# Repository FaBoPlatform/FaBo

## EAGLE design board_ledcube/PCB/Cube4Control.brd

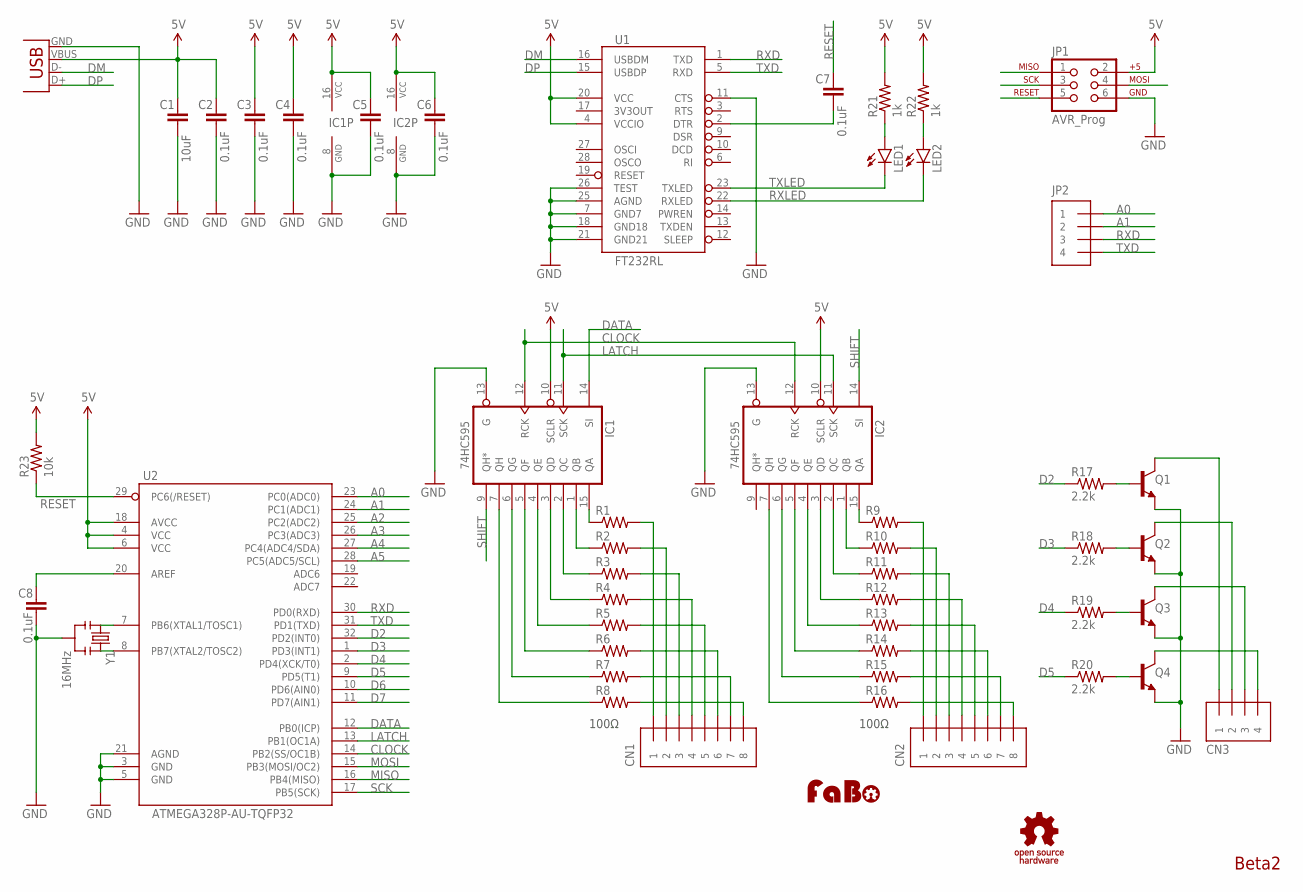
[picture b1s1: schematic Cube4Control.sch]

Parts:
C1: 10uF; EIA1206
C2, C3, C4, C5, C6, C7, C8: 0.1uF; EIA0603
CN1, CN2: PINHEAD-1X8; 1X8-SNEAKY
CN3: PINHEAD-1X4; 1X4-SNEAKY
IC1, IC2: 74HC595; SO16-3.9
JP1: AVR_Prog; TC2030-MCP
JP2: PINHEAD-1X4; 1X4-SNEAKY
LED1, LED2: LED-EIA0603; EIA0603-LED
Q1, Q2, Q3, Q4: NPN-2SC3325; SOT23-3
R1, R2, R3, R4, R5, R6, R7, R8, R9, R10, R11, R12, R13, R14, R15, R16: RES-EIA0603; EIA0603@1
R17, R18, R19, R20: 2.2k; EIA0603@1
R21, R22: 1k; EIA0603@1
R23: 10k; EIA0603@1
U1: FT232RL; SSOP28
U2: ATMEGA328P-AU-TQFP32; TQFP-32-08
U$2: LOGO_FABO-M; LOGO_FABO_M
U$4: LOGO_OSHW_T-M; LOGO_OSHW_T_M
USB1: USB-B-MICRO_SMD; USB_B_MICRO
Y1: 16MHz; RESONATOR_SMD

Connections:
5V: C1.1, C2.1, C3.1, C4.1, C5.1, C6.1, IC1.10 (SCLR), IC1.16 (VCC), IC2.10 (SCLR), IC2.16 (VCC), JP1.2, R21.2, R22.2, R23.2, U1.4 (VCCIO), U1.20 (VCC), U2.4 (VCC), U2.6 (VCC), U2.18 (AVCC), USB1.VBUS
A0: JP2.1, U2.23 (PC0(ADC0))
A1: JP2.2, U2.24 (PC1(ADC1))
A2: U2.25 (PC2(ADC2))
A3: U2.26 (PC3(ADC3))
A4: U2.27 (PC4(ADC4/SDA))
A5: U2.28 (PC5(ADC5/SCL))
AREF: C8.1, U2.20 (AREF)
CLOCK: IC1.12 (RCK), IC2.12 (RCK), U2.14 (PB2(SS/OC1B))
D2: R17.1, U2.32 (PD2(INT0))
D3: R18.1, U2.1 (PD3(INT1))
D4: R19.1, U2.2 (PD4(XCK/T0))
D5: R20.1, U2.9 (PD5(T1))
D6: U2.10 (PD6(AIN0))
D7: U2.11 (PD7(AIN1))
DATA: IC1.14 (SI), U2.12 (PB0(ICP))
DM: U1.16 (USBDM), USB1.D-
DP: U1.15 (USBDP), USB1.D+
DTR: C7.2, U1.2 (DTR)
GND: C1.2, C2.2, C3.2, C4.2, C5.2, C6.2, C8.2, IC1.8 (GND), IC1.13 (G), IC2.8 (GND), IC2.13 (G), JP1.6, Q1.2 (E), Q2.2 (E), Q3.2 (E), Q4.2 (E), U1.7 (GND7), U1.11 (CTS), U1.18 (GND18), U1.21 (GND21), U1.25 (AGND), U1.26 (TEST), U2.3 (GND), U2.5 (GND), U2.21 (AGND), USB1.GND, Y1.2
LATCH: IC1.11 (SCK), IC2.11 (SCK), U2.13 (PB1(OC1A))
MISO: JP1.1, U2.16 (PB4(MISO))
MOSI: JP1.4, U2.15 (PB3(MOSI/OC2))
unnamed: LED1.A, R21.1
unnamed: CN3.1, Q1.3 (C)
unnamed: CN3.2, Q2.3 (C)
unnamed: CN3.3, Q3.3 (C)
unnamed: U2.7 (PB6(XTAL1/TOSC1)), Y1.1
unnamed: U2.8 (PB7(XTAL2/TOSC2)), Y1.3
unnamed: CN3.4, Q4.3 (C)
unnamed: Q1.1 (B), R17.2
unnamed: Q2.1 (B), R18.2
unnamed: Q3.1 (B), R19.2
unnamed: Q4.1 (B), R20.2
unnamed: CN2.1, R9.2
unnamed: CN2.2, R10.2
unnamed: CN2.3, R11.2
unnamed: CN2.4, R12.2
unnamed: CN2.5, R13.2
unnamed: CN2.6, R14.2
unnamed: CN2.7, R15.2
unnamed: CN2.8, R16.2
unnamed: IC2.15 (QA), R9.1
unnamed: IC2.1 (QB), R10.1
unnamed: IC2.2 (QC), R11.1
unnamed: IC2.3 (QD), R12.1
unnamed: IC2.4 (QE), R13.1
unnamed: IC2.5 (QF), R14.1
unnamed: IC2.6 (QG), R15.1
unnamed: IC1.15 (QA), R1.1
unnamed: IC1.1 (QB), R2.1
unnamed: LED2.A, R22.1
unnamed: IC1.2 (QC), R3.1
unnamed: IC1.3 (QD), R4.1
unnamed: IC2.7 (QH), R16.1
unnamed: IC1.4 (QE), R5.1
unnamed: IC1.5 (QF), R6.1
unnamed: IC1.6 (QG), R7.1
unnamed: IC1.7 (QH), R8.1
unnamed: CN1.1, R1.2
unnamed: CN1.2, R2.2
unnamed: CN1.3, R3.2
unnamed: CN1.4, R4.2
unnamed: CN1.5, R5.2
unnamed: CN1.6, R6.2
unnamed: CN1.7, R7.2
unnamed: CN1.8, R8.2
RESET: C7.1, JP1.5, R23.1, U2.29 (PC6(/RESET))
RXD: JP2.3, U1.1 (TXD), U2.30 (PD0(RXD))
RXLED: LED2.C, U1.22 (RXLED)
SCK: JP1.3, U2.17 (PB5(SCK))
SHIFT: IC1.9 (QH*), IC2.14 (SI)
TXD: JP2.4, U1.5 (RXD), U2.31 (PD1(TXD))
TXLED: LED1.C, U1.23 (TXLED)

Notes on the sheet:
Beta2
100Ω

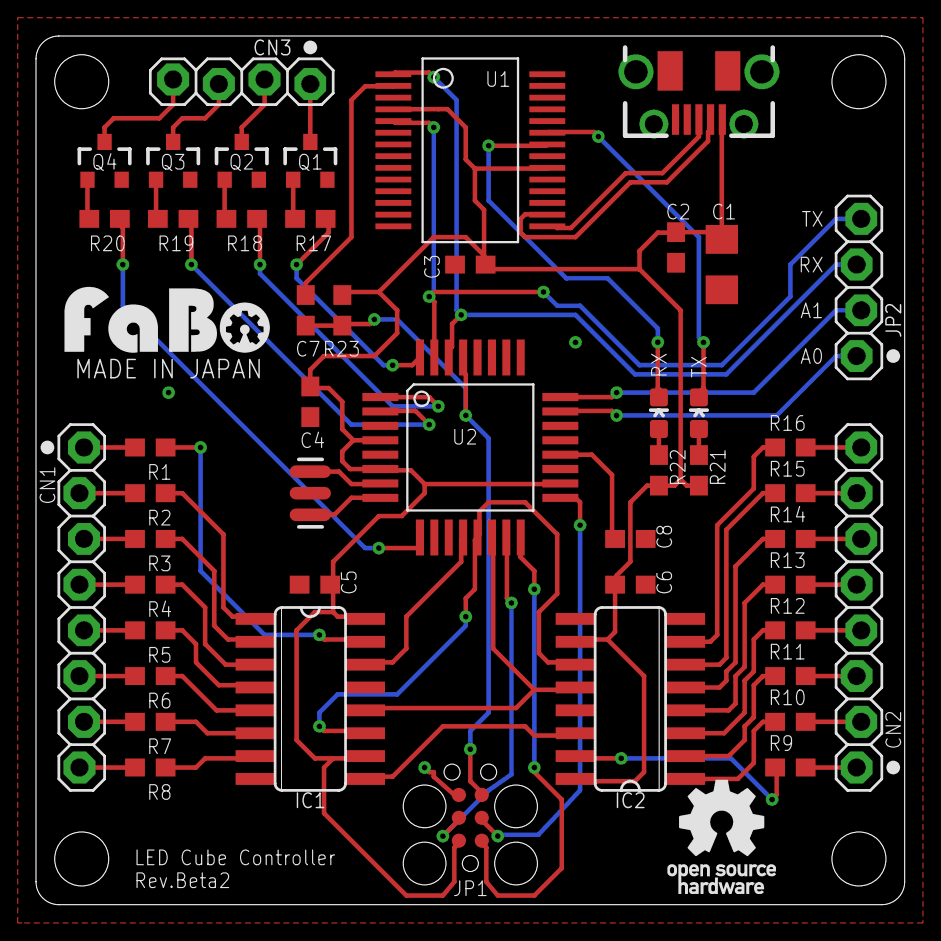
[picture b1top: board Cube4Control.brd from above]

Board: 2 copper layers, 48.3 x 48.3 mm, 50 parts (0 on the bottom side), 68 nets.

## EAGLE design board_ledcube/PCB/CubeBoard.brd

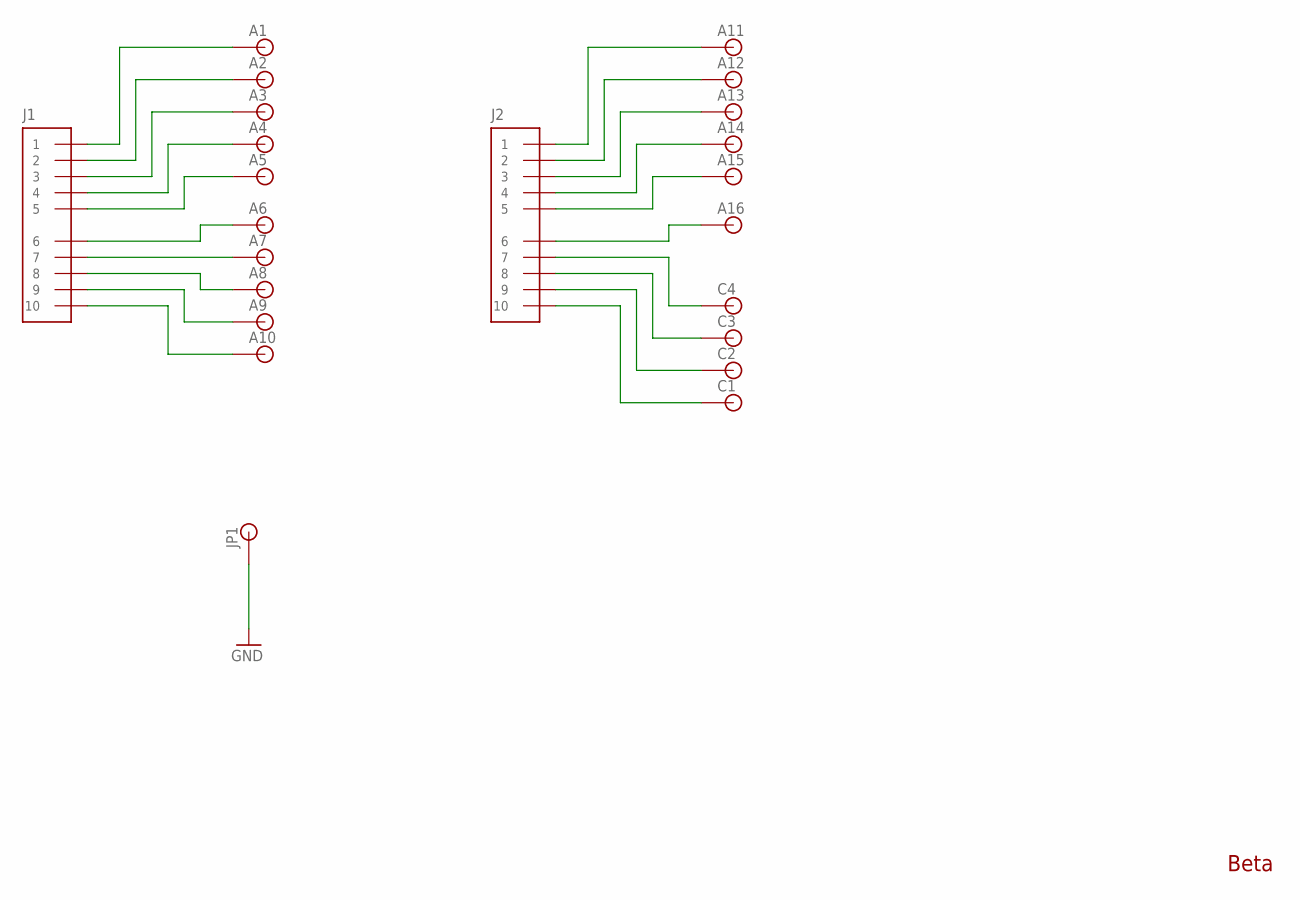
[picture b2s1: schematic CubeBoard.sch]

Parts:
A1: anode1; PIN-1X1
A2: anode2; PIN-1X1
A3: anode3; PIN-1X1
A4: anode4; PIN-1X1
A5: anode5; PIN-1X1
A6: anode6; PIN-1X1
A7: anode7; PIN-1X1
A8: anode8; PIN-1X1
A9: anode9; PIN-1X1
A10: anode10; PIN-1X1
A11: anode11; PIN-1X1
A12: anode12; PIN-1X1
A13: anode13; PIN-1X1
A14: anode14; PIN-1X1
A15: anode15; PIN-1X1
A16: anode16; PIN-1X1
C1: cathode1; PIN-1X1
C2: cathode2; PIN-1X1
C3: cathode3; PIN-1X1
C4: cathode4; PIN-1X1
J1, J2: PINHEAD-1X10; 1X10-SNEAKY
JP1: PIN-1X1

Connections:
GND: JP1.1
unnamed: A1.1, J1.1
unnamed: A2.1, J1.2
unnamed: A3.1, J1.3
unnamed: A4.1, J1.4
unnamed: A5.1, J1.5
unnamed: A6.1, J1.6
unnamed: A7.1, J1.7
unnamed: A8.1, J1.8
unnamed: A9.1, J1.9
unnamed: A10.1, J1.10
unnamed: A11.1, J2.1
unnamed: A12.1, J2.2
unnamed: A13.1, J2.3
unnamed: A14.1, J2.4
unnamed: A15.1, J2.5
unnamed: A16.1, J2.6
unnamed: C4.1, J2.7
unnamed: C3.1, J2.8
unnamed: C2.1, J2.9
unnamed: C1.1, J2.10

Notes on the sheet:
Beta

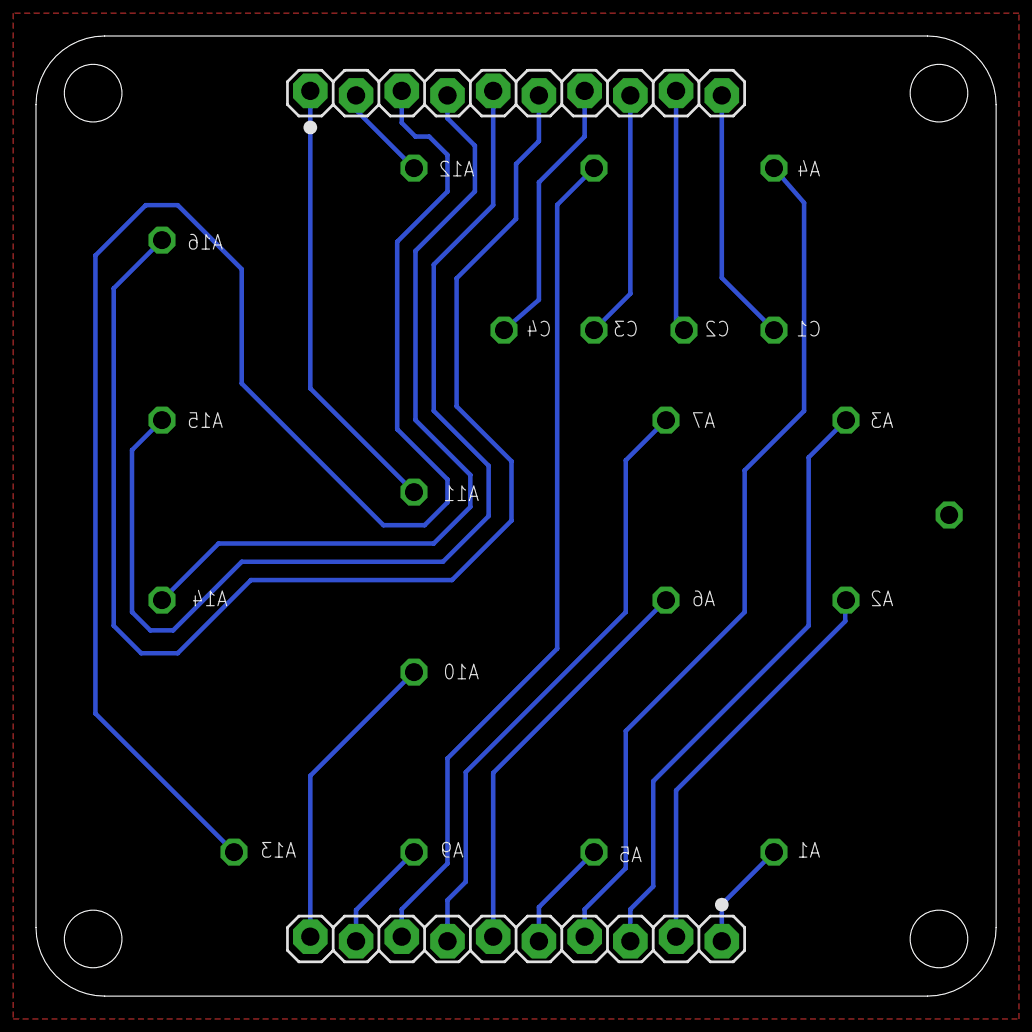
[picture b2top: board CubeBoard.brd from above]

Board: 2 copper layers, 53.3 x 53.3 mm, 23 parts (0 on the bottom side), 20 nets.

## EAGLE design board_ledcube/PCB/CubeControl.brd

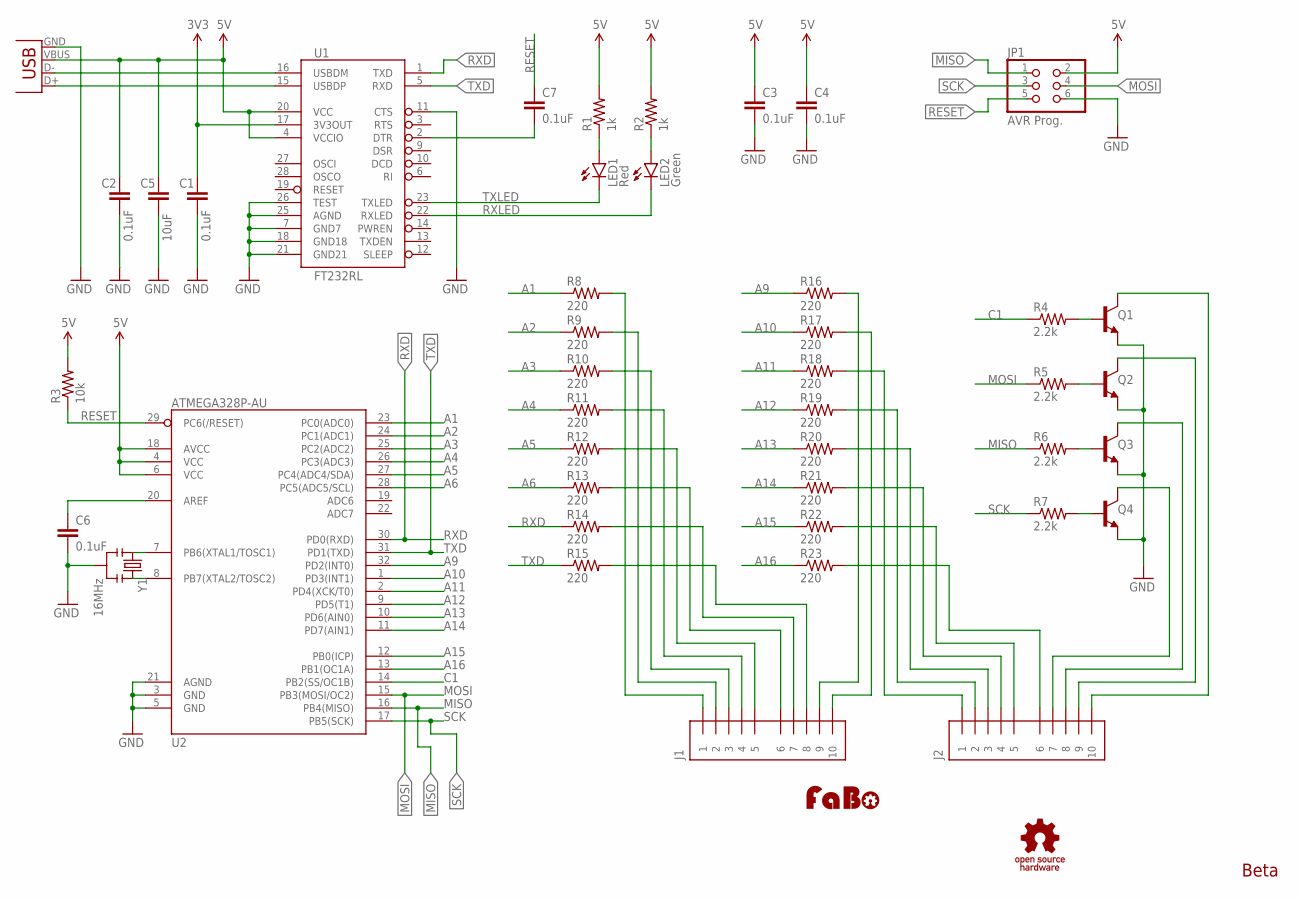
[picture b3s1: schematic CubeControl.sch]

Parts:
C1, C2, C3, C4, C6, C7: 0.1uF; EIA0603-CAP
C5: 10uF; EIA1206@1
J1, J2: PINHEAD-1X10; 1X10-SNEAKY
JP1: AVR Prog.; 2X03
LED1: Red; EIA0603-LED
LED2: Green; EIA0603-LED
Q1, Q2, Q3, Q4: NPN-2SC3325; SOT23-3
R1, R2: 1k; EIA0603-RES
R3: 10k; EIA0603-RES
R4, R5, R6, R7: 2.2k; EIA0603
R8, R9, R10, R11, R12, R13, R14, R15, R16, R17, R18, R19, R20, R21, R22, R23: 220; EIA0603
U1: FT232RL; SSOP28
U2: ATMEGA328P-AU; TQFP-32-08
U$2: LOGO_OSHW_T-S; LOGO_OSHW_T_S
U$3: LOGO_FABO-M; LOGO_FABO_M
USB1: USB-B-MICRO_SMD; USB_B_MICRO
Y1: 16MHz; RESONATOR_SMD

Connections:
3V3: C1.1, U1.17 (3V3OUT)
5V: C2.1, C3.1, C4.1, C5.1, JP1.2, R1.2, R2.2, R3.2, U1.4 (VCCIO), U1.20 (VCC), U2.4 (VCC), U2.6 (VCC), U2.18 (AVCC), USB1.VBUS
A1: R8.1, U2.23 (PC0(ADC0))
A2: R9.1, U2.24 (PC1(ADC1))
A3: R10.1, U2.25 (PC2(ADC2))
A4: R11.1, U2.26 (PC3(ADC3))
A5: R12.1, U2.27 (PC4(ADC4/SDA))
A6: R13.1, U2.28 (PC5(ADC5/SCL))
A9: R16.1, U2.32 (PD2(INT0))
A10: R17.1, U2.1 (PD3(INT1))
A11: R18.1, U2.2 (PD4(XCK/T0))
A12: R19.1, U2.9 (PD5(T1))
A13: R20.1, U2.10 (PD6(AIN0))
A14: R21.1, U2.11 (PD7(AIN1))
A15: R22.1, U2.12 (PB0(ICP))
A16: R23.1, U2.13 (PB1(OC1A))
C1: R4.1, U2.14 (PB2(SS/OC1B))
GND: C1.2, C2.2, C3.2, C4.2, C5.2, C6.2, JP1.6, Q1.2 (E), Q2.2 (E), Q3.2 (E), Q4.2 (E), U1.7 (GND7), U1.11 (CTS), U1.18 (GND18), U1.21 (GND21), U1.25 (AGND), U1.26 (TEST), U2.3 (GND), U2.5 (GND), U2.21 (AGND), USB1.GND, Y1.2
MISO: JP1.1, R6.1, U2.16 (PB4(MISO))
MOSI: JP1.4, R5.1, U2.15 (PB3(MOSI/OC2))
unnamed: LED1.A, R1.1
unnamed: LED2.A, R2.1
unnamed: J1.1, R8.2
unnamed: J1.2, R9.2
unnamed: U2.7 (PB6(XTAL1/TOSC1)), Y1.1
unnamed: U2.8 (PB7(XTAL2/TOSC2)), Y1.3
unnamed: C6.1, U2.20 (AREF)
unnamed: J1.3, R10.2
unnamed: J1.4, R11.2
unnamed: J1.5, R12.2
unnamed: J1.6, R13.2
unnamed: J1.7, R14.2
unnamed: J1.8, R15.2
unnamed: J1.9, R16.2
unnamed: J1.10, R17.2
unnamed: J2.1, R18.2
unnamed: J2.2, R19.2
unnamed: J2.3, R20.2
unnamed: J2.4, R21.2
unnamed: J2.5, R22.2
unnamed: J2.6, R23.2
unnamed: C7.2, U1.2 (DTR)
unnamed: J2.10, Q1.3 (C)
unnamed: J2.9, Q2.3 (C)
unnamed: J2.8, Q3.3 (C)
unnamed: J2.7, Q4.3 (C)
unnamed: Q4.1 (B), R7.2
unnamed: Q3.1 (B), R6.2
unnamed: Q2.1 (B), R5.2
unnamed: Q1.1 (B), R4.2
RESET: C7.1, JP1.5, R3.1, U2.29 (PC6(/RESET))
RXD: R14.1, U1.1 (TXD), U2.30 (PD0(RXD))
RXLED: LED2.C, U1.22 (RXLED)
SCK: JP1.3, R7.1, U2.17 (PB5(SCK))
TXD: R15.1, U1.5 (RXD), U2.31 (PD1(TXD))
TXLED: LED1.C, U1.23 (TXLED)
USB_D+: U1.15 (USBDP), USB1.D+
USB_D-: U1.16 (USBDM), USB1.D-

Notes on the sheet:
Beta

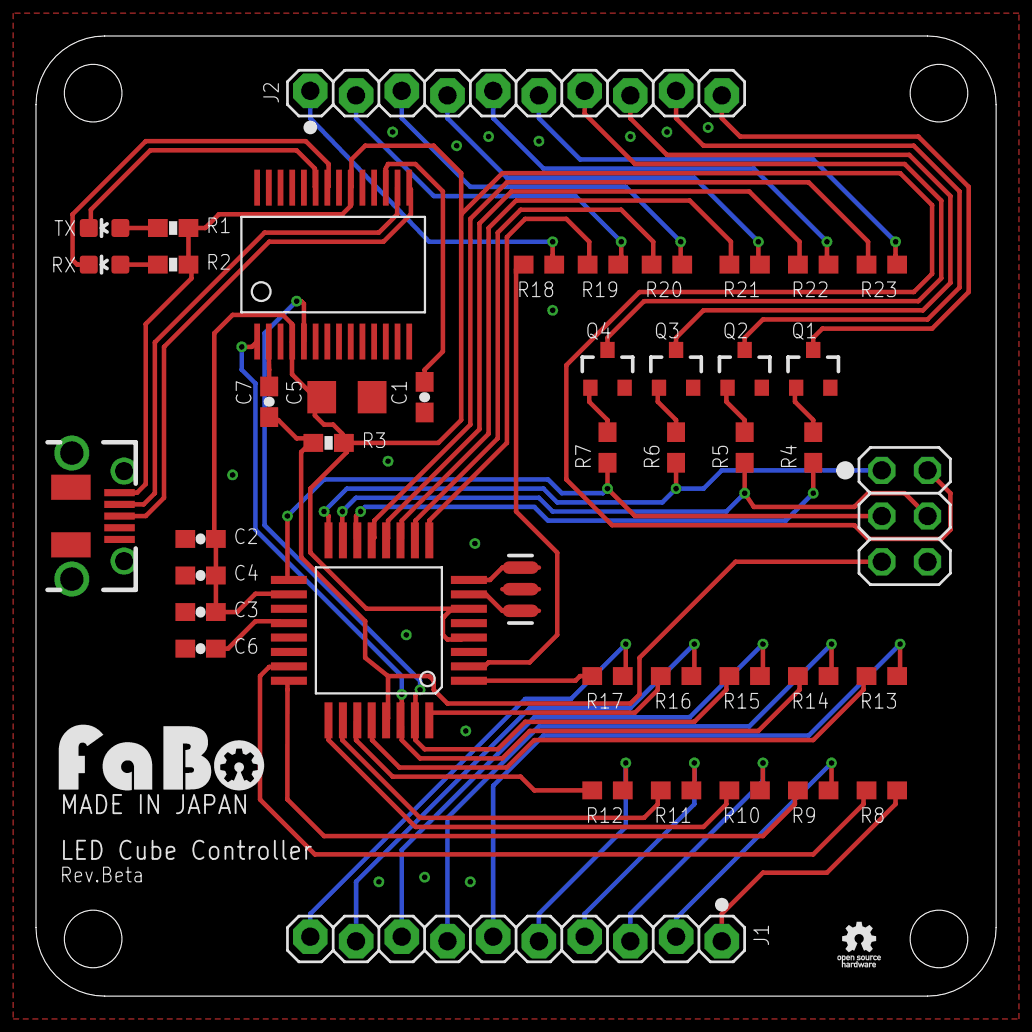
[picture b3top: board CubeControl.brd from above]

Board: 2 copper layers, 53.3 x 53.3 mm, 45 parts (0 on the bottom side), 58 nets.

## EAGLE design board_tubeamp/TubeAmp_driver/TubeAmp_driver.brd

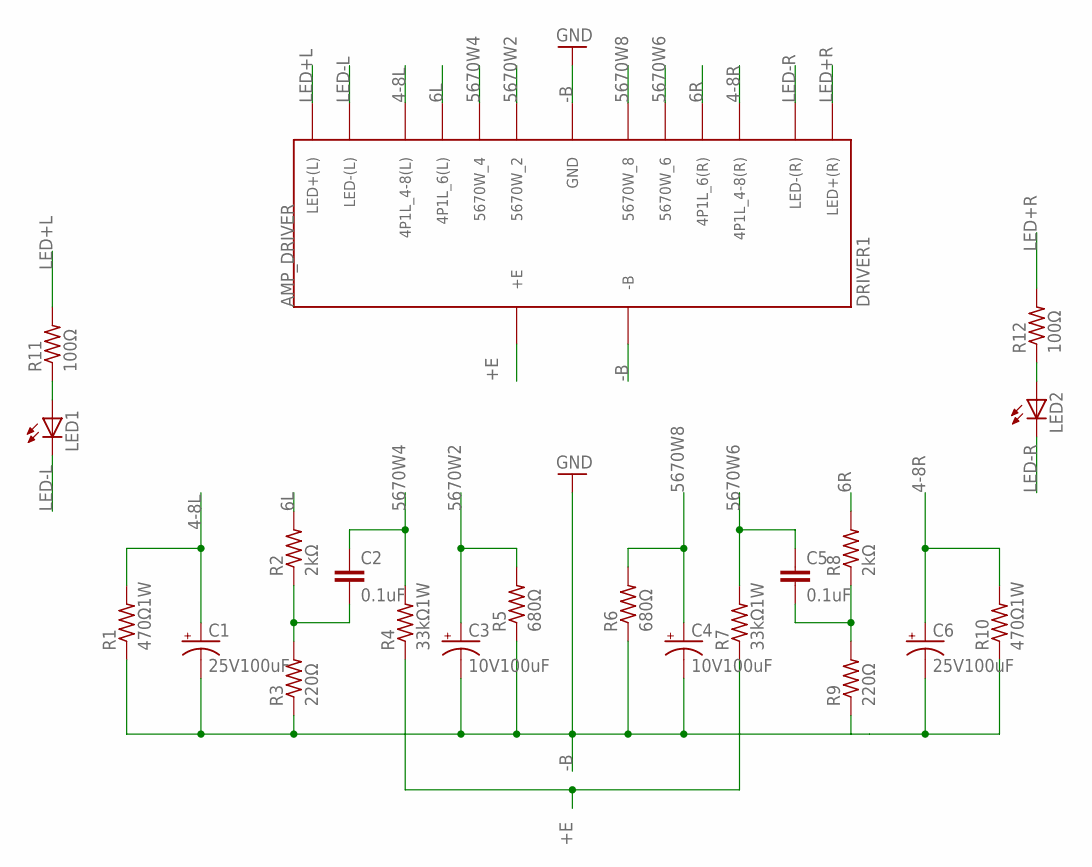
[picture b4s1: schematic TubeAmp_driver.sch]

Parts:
C1, C6: 25V100uF; 100UF25V_S3_NO_VALUE
C2, C5: 0.1uF; C12.5B6_NO_VALUE
C3, C4: 10V100uF; 100UF25V_S3_NO_VALUE
DRIVER1: AMP_DRIVER
LED1, LED2: LED; LED3MM
R1, R10: 470Ω1W; RESISTOR_1W
R2, R8: 2kΩ; RESISTOR_1/4W
R3, R9: 220Ω; RESISTOR_1/4W
R4, R7: 33kΩ1W; RESISTOR_1W
R5, R6: 680Ω; RESISTOR_1/4W
R11, R12: 100Ω; RESISTOR_1/4W

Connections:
4-8L: C1.1 (+), DRIVER1.4P1L_4-8L (4P1L_4-8(L)), R1.2
4-8R: C6.1 (+), DRIVER1.4P1L_4-8R (4P1L_4-8(R)), R10.2
6L: DRIVER1.4P1L_6L (4P1L_6(L)), R2.2
6R: DRIVER1.4P1L_6R (4P1L_6(R)), R8.2
5670W2: C3.1 (+), DRIVER1.5670W_2, R5.2
5670W4: C2.1, DRIVER1.5670W_4, R4.2
5670W6: C5.1, DRIVER1.5670W_6, R7.2
5670W8: C4.1 (+), DRIVER1.5670W_8, R6.2
+E: DRIVER1.+E, R4.1, R7.1
-B: C1.2 (-), C3.2 (-), C4.2 (-), C6.2 (-), DRIVER1.-B, DRIVER1.GND, R1.1, R3.1, R5.1, R6.1, R9.1, R10.1
LED+L: DRIVER1.LED+_L (LED+(L)), R11.2
LED+R: DRIVER1.LED+_R (LED+(R)), R12.2
LED-L: DRIVER1.LED-_L (LED-(L)), LED1.K (C)
LED-R: DRIVER1.LED-_R (LED-(R)), LED2.K (C)
unnamed: C2.2, R2.1, R3.2
unnamed: LED1.A, R11.1
unnamed: LED2.A, R12.1
unnamed: C5.2, R8.1, R9.2

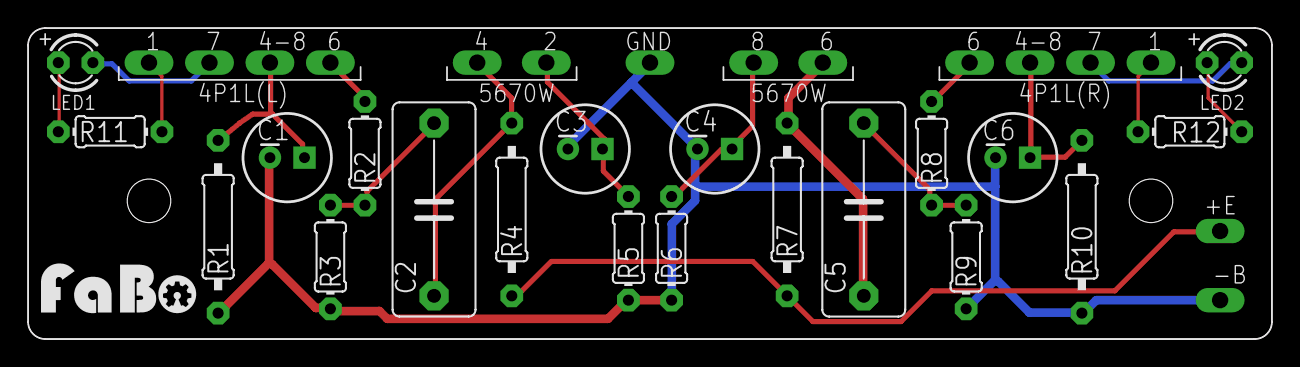
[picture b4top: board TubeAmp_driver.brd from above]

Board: 2 copper layers, 91.4 x 22.9 mm, 22 parts (0 on the bottom side), 18 nets.

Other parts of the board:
U$1: LOGO_FABO_M

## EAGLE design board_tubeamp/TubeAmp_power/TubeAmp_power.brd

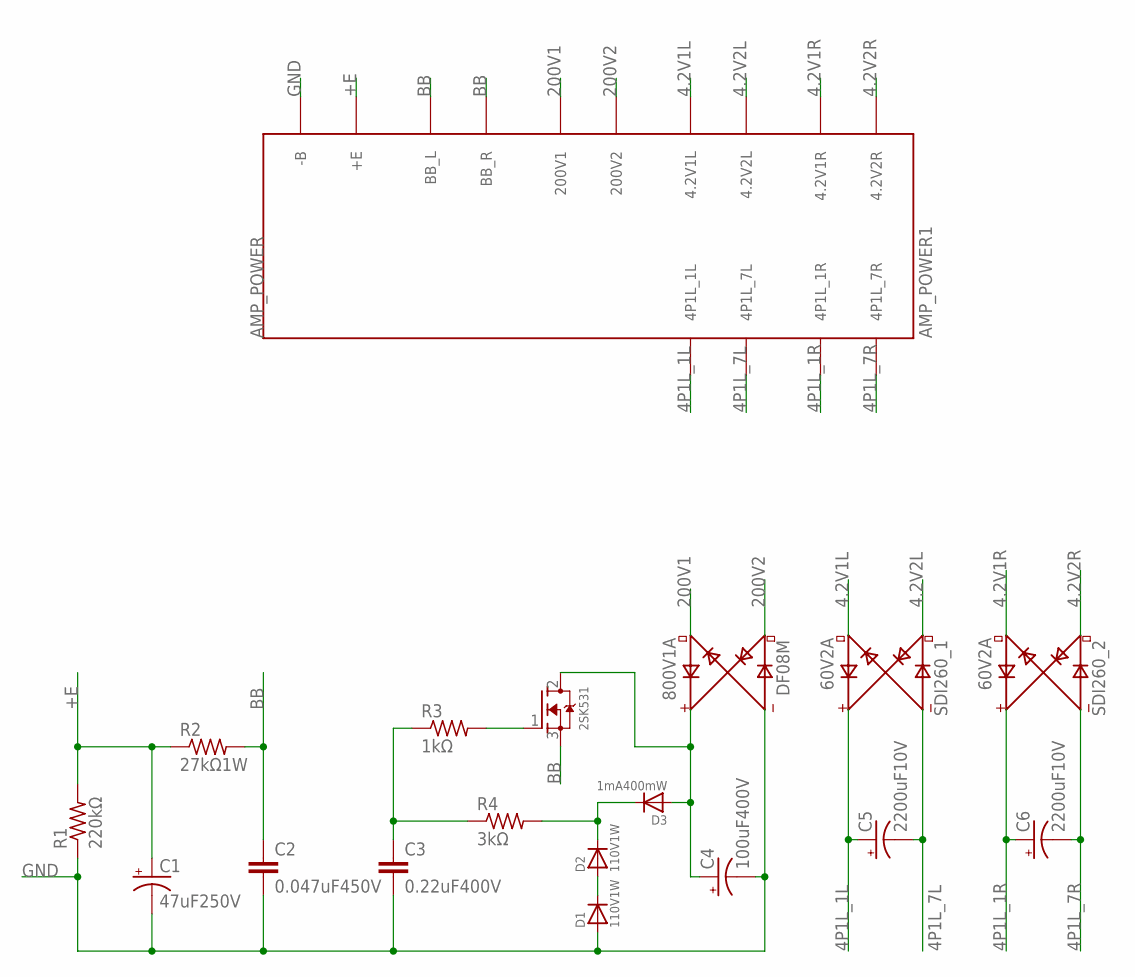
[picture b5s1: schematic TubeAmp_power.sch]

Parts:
2SK531: MOSFET_NN-CHANNEL; MOSFET-N
AMP_POWER1: AMP_POWER
C1: 47uF250V; 47UF250V_S5_NO_VALUE
C2: 0.047uF450V; C15B6_NO_VALUE
C3: 0.22uF400V; C10B6_NO_VALUE
C4: 100uF400V; 100UF400V_S6_NO_VALUE
C5, C6: 2200uF10V; 47UF250V_S5_NO_VALUE
D1, D2: 110V1W; DIODE_NO_VALUE
D3: 1mA400mW; DIODE_NO_VALUE
DF08M: 800V1A; RECTIFER
R1: 220kΩ; RESISTOR_1/2W
R2: 27kΩ1W; RESISTOR_1W
R3: 1kΩ; RESISTOR_1/4W
R4: 3kΩ; RESISTOR_1/4W
SDI260_1, SDI260_2: 60V2A; RECTIFER

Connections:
4.2V1L: AMP_POWER1.4.2V1(L) (4.2V1L), SDI260_1.AC2
4.2V1R: AMP_POWER1.4.2V1(R) (4.2V1R), SDI260_2.AC2
4.2V2L: AMP_POWER1.4.2V2(L) (4.2V2L), SDI260_1.AC1
4.2V2R: AMP_POWER1.4.2V2(R) (4.2V2R), SDI260_2.AC1
4P1L_1L: AMP_POWER1.4P1L_1(L) (4P1L_1L), C5.1 (+), SDI260_1.+
4P1L_1R: AMP_POWER1.4P1L_1(R) (4P1L_1R), C6.1 (+), SDI260_2.+
4P1L_7L: AMP_POWER1.4P1L_7(L) (4P1L_7L), C5.2 (-), SDI260_1.-
4P1L_7R: AMP_POWER1.4P1L_7(R) (4P1L_7R), C6.2 (-), SDI260_2.-
200V1: AMP_POWER1.200V1, DF08M.AC2
200V2: AMP_POWER1.200V2, DF08M.AC1
+E: AMP_POWER1.+E, C1.1 (+), R1.2, R2.1
BB: 2SK531.3 (S), AMP_POWER1.BB(L) (BB_L), AMP_POWER1.BB(R) (BB_R), C2.1, R2.2
GND: AMP_POWER1.-B, C1.2 (-), C2.2, C3.2, C4.2 (-), D1.A, DF08M.-, R1.1
unnamed: 2SK531.1 (G), R3.2
unnamed: 2SK531.2 (D), C4.1 (+), D3.A, DF08M.+
unnamed: C3.1, R3.1, R4.1
unnamed: D2.K, D3.K, R4.2
unnamed: D1.K, D2.A

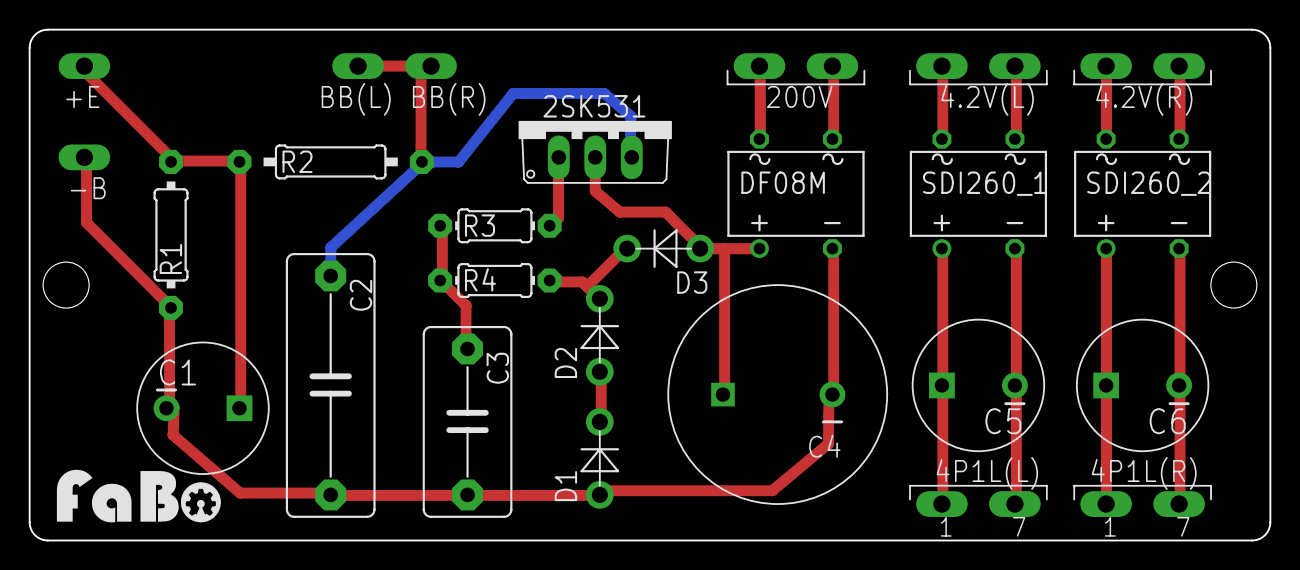
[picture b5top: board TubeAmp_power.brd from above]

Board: 2 copper layers, 86.4 x 35.6 mm, 19 parts (0 on the bottom side), 18 nets.

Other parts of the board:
U$1: LOGO_FABO_M

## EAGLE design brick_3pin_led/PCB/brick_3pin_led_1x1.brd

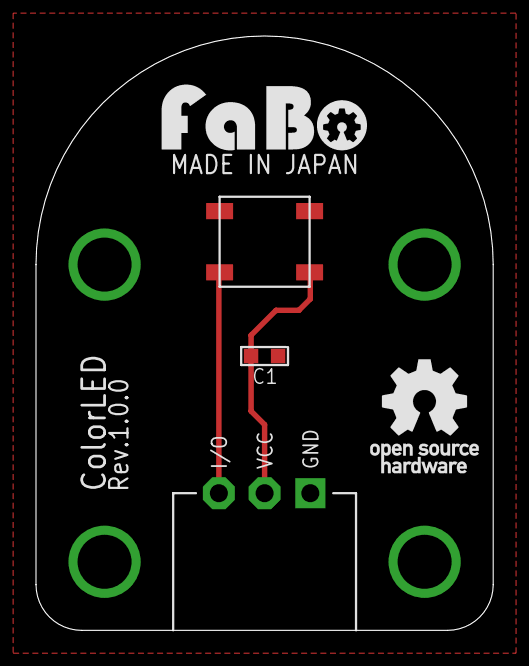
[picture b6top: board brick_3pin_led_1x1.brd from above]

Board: 2 copper layers, 25.4 x 33.0 mm, 5 parts (0 on the bottom side), 3 nets.

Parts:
C1: 0.1uf; 0603
J1: FABO_BRICK_3PIN
LED1: WS2818B
U$2: LOGO_FABO_M
U$5: LOGO_OSHW_T_M

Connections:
+5V: C1.2, J1.VCC, LED1.1
DI_1: J1.IN/OUT, LED1.4
GND: C1.1, J1.GND, LED1.3

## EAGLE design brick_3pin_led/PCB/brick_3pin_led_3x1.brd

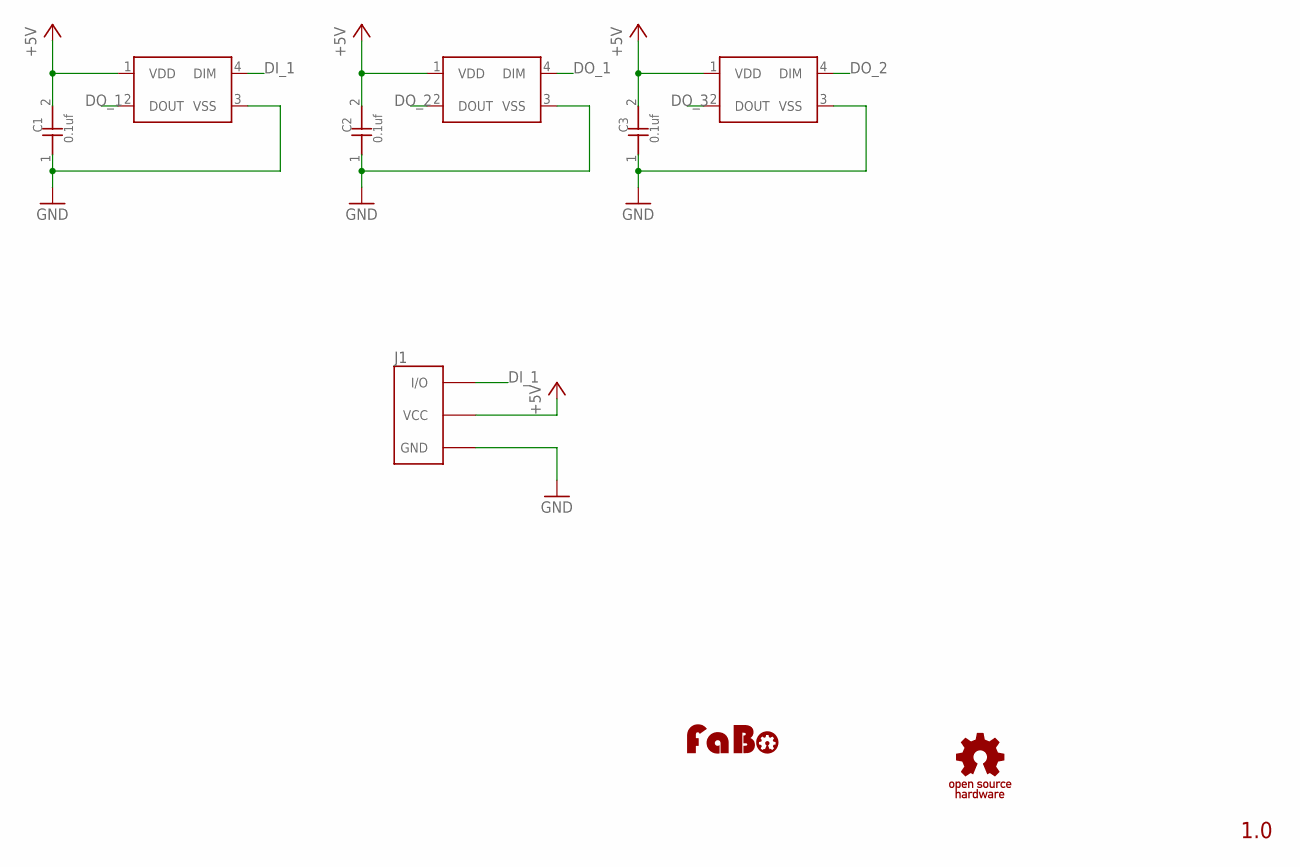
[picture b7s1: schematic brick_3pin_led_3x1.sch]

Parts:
C1, C2, C3: 0.1uf; 0603
J1: BRICK_3PIN_MIDDLE
LED1, LED2, LED3: WS2818B
U$4: LOGO_FABO-M; LOGO_FABO_M
U$5: LOGO_OSHW_T-M; LOGO_OSHW_T_M

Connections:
+5V: C1.2, C2.2, C3.2, J1.VCC, LED1.1 (VDD), LED2.1 (VDD), LED3.1 (VDD)
DI_1: J1.IN/OUT (I/O), LED1.4 (DIM)
DO_1: LED1.2 (DOUT), LED2.4 (DIM)
DO_2: LED2.2 (DOUT), LED3.4 (DIM)
DO_3: LED3.2 (DOUT)
GND: C1.1, C2.1, C3.1, J1.GND, LED1.3 (VSS), LED2.3 (VSS), LED3.3 (VSS)

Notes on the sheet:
1.0

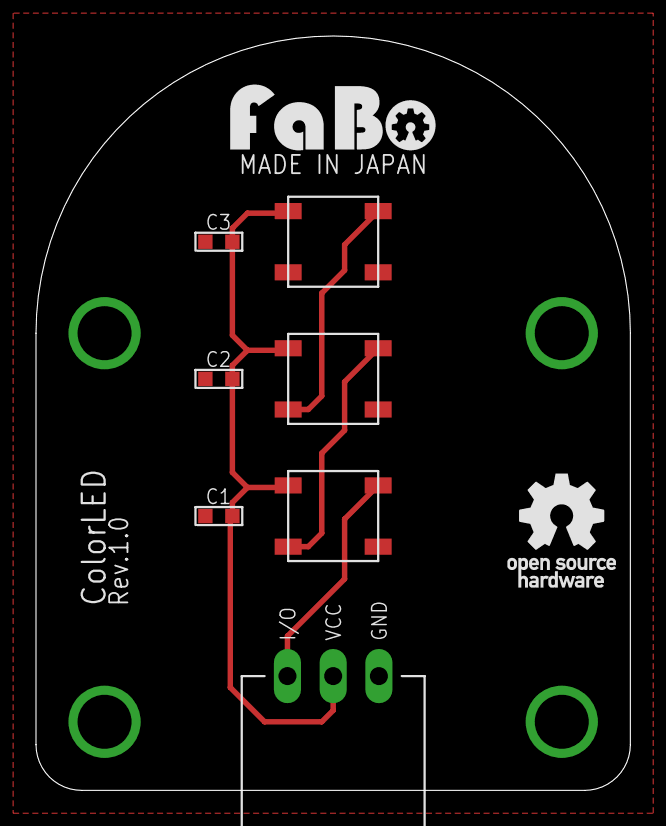
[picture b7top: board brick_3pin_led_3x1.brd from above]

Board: 2 copper layers, 33.0 x 41.9 mm, 9 parts (0 on the bottom side), 5 nets.

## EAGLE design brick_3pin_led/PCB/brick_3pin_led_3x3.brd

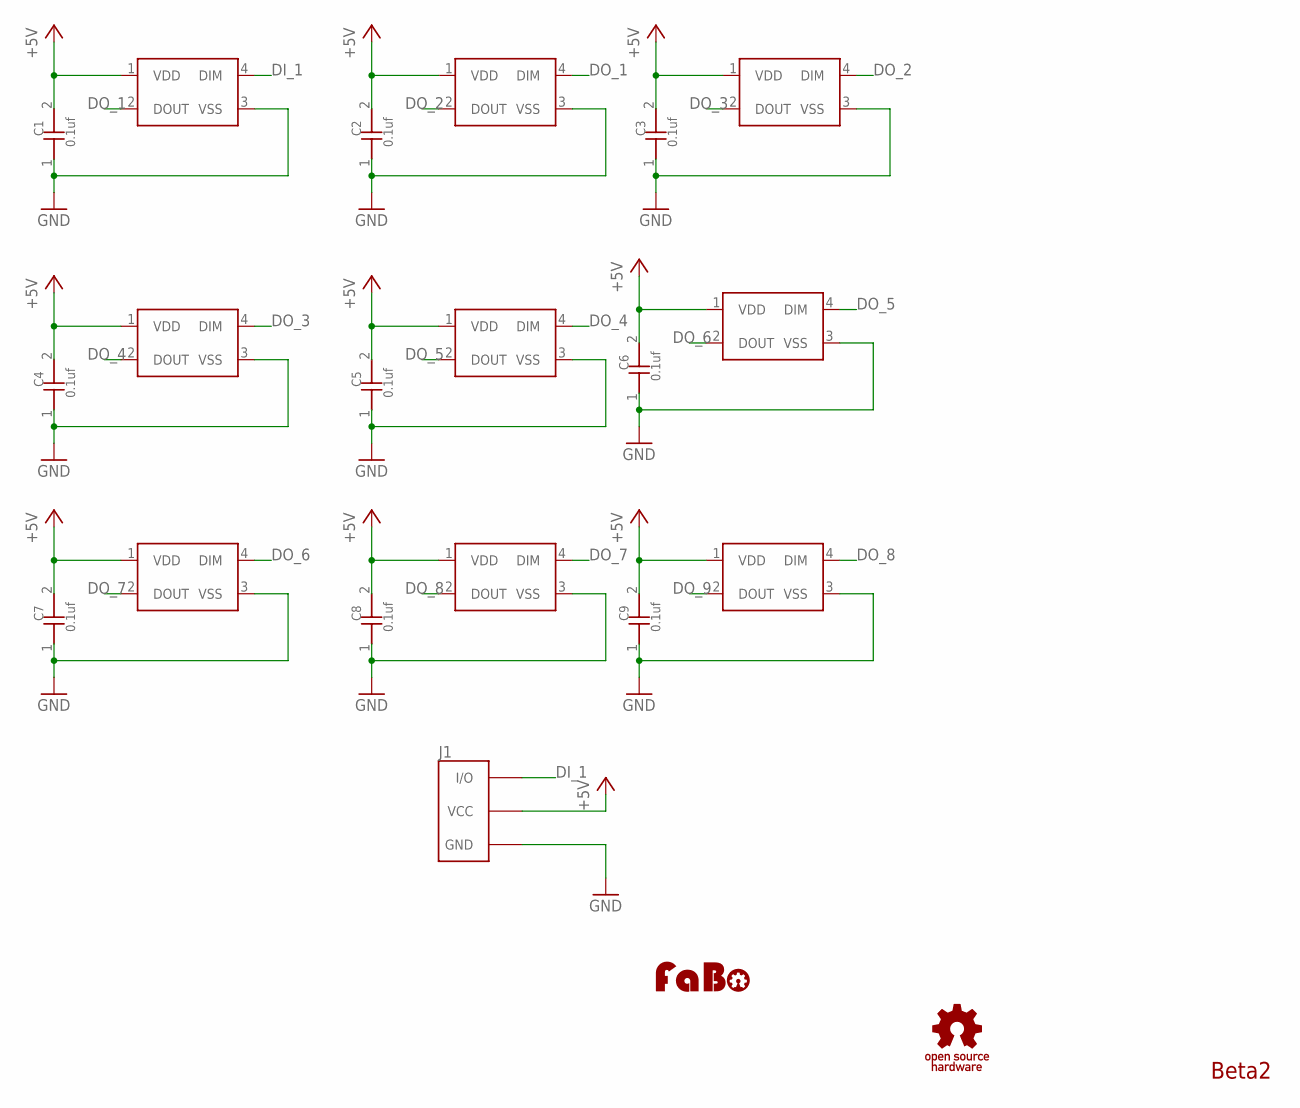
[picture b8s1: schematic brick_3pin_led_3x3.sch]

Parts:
C1, C2, C3, C4, C5, C6, C7, C8, C9: 0.1uf; 0603
J1: BRICK_3PIN_BIG
LED1, LED2, LED3, LED4, LED5, LED6, LED7, LED8, LED9: WS2818B
U$4: LOGO_OSHW_T-M; LOGO_OSHW_T_M
U$5: LOGO_FABO-M; LOGO_FABO_M

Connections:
+5V: C1.2, C2.2, C3.2, C4.2, C5.2, C6.2, C7.2, C8.2, C9.2, J1.VCC, LED1.1 (VDD), LED2.1 (VDD), LED3.1 (VDD), LED4.1 (VDD), LED5.1 (VDD), LED6.1 (VDD), LED7.1 (VDD), LED8.1 (VDD), LED9.1 (VDD)
DI_1: J1.IN/OUT (I/O), LED1.4 (DIM)
DO_1: LED1.2 (DOUT), LED2.4 (DIM)
DO_2: LED2.2 (DOUT), LED3.4 (DIM)
DO_3: LED3.2 (DOUT), LED4.4 (DIM)
DO_4: LED4.2 (DOUT), LED5.4 (DIM)
DO_5: LED5.2 (DOUT), LED6.4 (DIM)
DO_6: LED6.2 (DOUT), LED7.4 (DIM)
DO_7: LED7.2 (DOUT), LED8.4 (DIM)
DO_8: LED8.2 (DOUT), LED9.4 (DIM)
DO_9: LED9.2 (DOUT)
GND: C1.1, C2.1, C3.1, C4.1, C5.1, C6.1, C7.1, C8.1, C9.1, J1.GND, LED1.3 (VSS), LED2.3 (VSS), LED3.3 (VSS), LED4.3 (VSS), LED5.3 (VSS), LED6.3 (VSS), LED7.3 (VSS), LED8.3 (VSS), LED9.3 (VSS)

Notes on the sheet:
Beta2

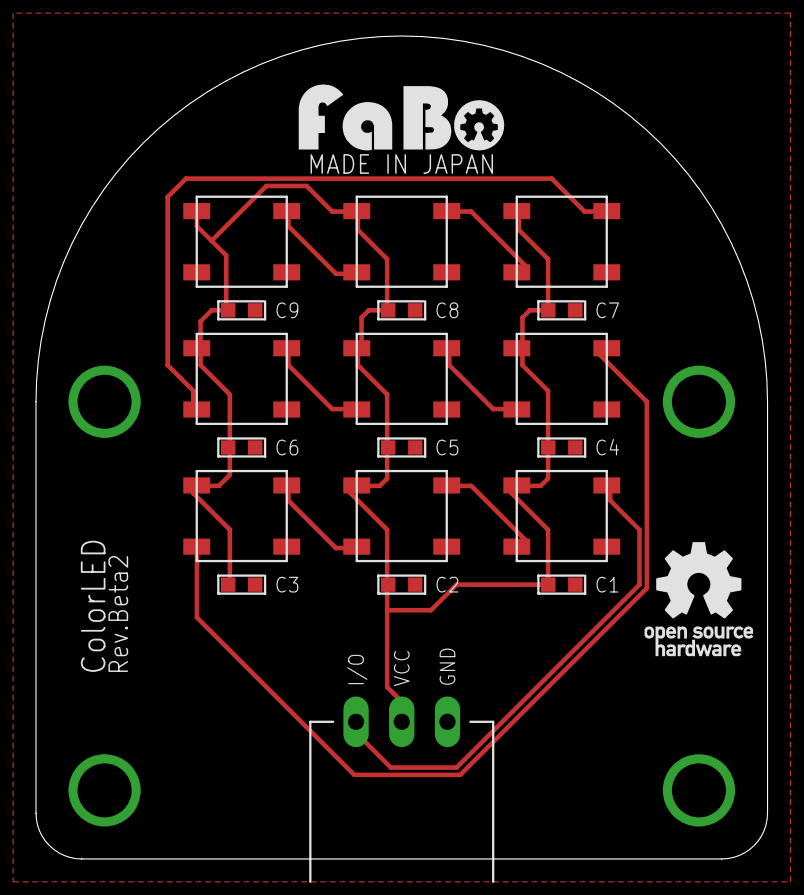
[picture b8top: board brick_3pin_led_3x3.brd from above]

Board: 2 copper layers, 40.6 x 45.7 mm, 21 parts (0 on the bottom side), 11 nets.

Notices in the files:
parts and their libraries:
FaBo-etc: Released under the Creative Commons Attribution-ShareAlike 4.0 License
https://creativecommons.org/licenses/by-sa/4.0
